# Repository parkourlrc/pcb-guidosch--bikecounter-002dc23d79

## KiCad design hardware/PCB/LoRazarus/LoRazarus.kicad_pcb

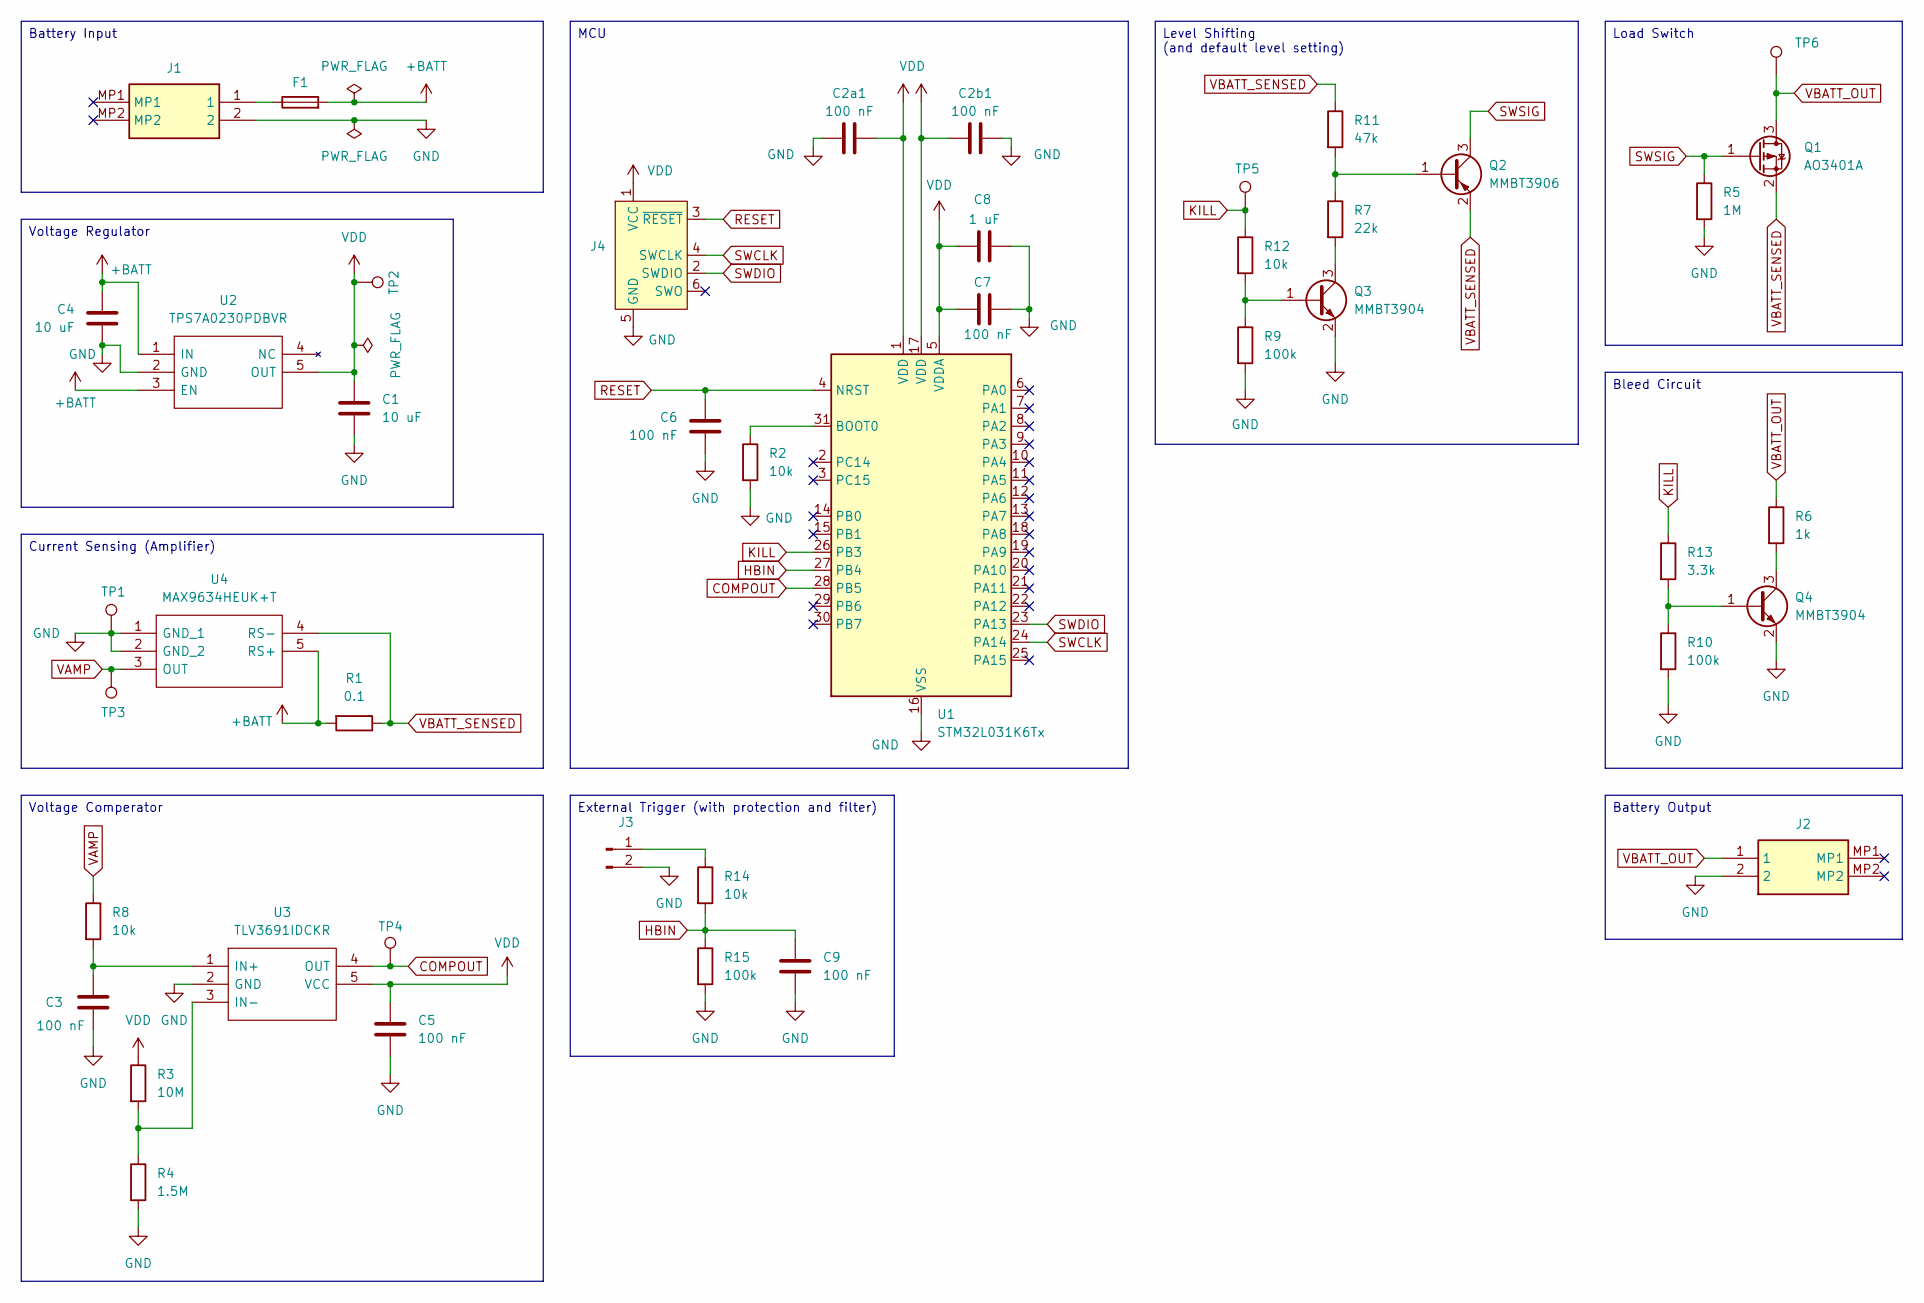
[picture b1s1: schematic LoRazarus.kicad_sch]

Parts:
C1, C4: 10 uF; C_0805_2012Metric
C2a1, C2b1, C3, C5, C6, C7, C9: 100 nF; C_0603_1608Metric
C8: 1 uF; C_0603_1608Metric
F1: Fuse; Fuse_1206_3216Metric
J1, J2: S2B-PH-SM4-TB_LF__SN_; S2BPHSM4TBLFSN; Mouser Part Number N/A
J3: Conn_01x02_Pin; PinHeader_1x02_P2.54mm_Vertical
J4: Conn_ARM_SWD_TagConnect_TC2030-NL; Tag-Connect_TC2030-IDC-NL_2x03_P1.27mm_Vertical
Q1: AO3401A; SOT-23
Q2: MMBT3906; SOT-23
Q3, Q4: MMBT3904; SOT-23
R1: 0.1; R_1206_3216Metric
R2, R8, R12, R14: 10k; R_0603_1608Metric
R3: 10M; R_0603_1608Metric
R4: 1.5M; R_0603_1608Metric
R5: 1M; R_0603_1608Metric
R6: 1k; R_0603_1608Metric
R7: 22k; R_0603_1608Metric
R9, R10, R15: 100k; R_0603_1608Metric
R11: 47k; R_0603_1608Metric
R13: 3.3k; R_0603_1608Metric
TP1, TP2, TP3, TP4, TP5, TP6: TestPoint; TestPoint_Pad_1.0x1.0mm
U1: STM32L031K6Tx; LQFP-32_7x7mm_P0.8mm
U2: TPS7A0230PDBVR; SOT-23-5; Mouser Part Number 595-TPS7A0230PDBVR
U3: TLV3691IDCKR; SOT-353_SC-70-5; Mouser Part Number 595-TLV3691IDCKR
U4: MAX9634HEUK+T; SOT-23-5; Mouser Part Number 700-MAX9634HEUKT

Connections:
+BATT: C4.1, F1.2, R1.2, U2.1 (IN), U2.3 (EN), U4.5 (RS+)
COMPOUT: TP4.1 (1_1), U1.28 (PB5), U3.4 (OUT)
GND: C1.2, C2a1.2, C2b1.2, C3.2, C4.2, C5.2, C6.2, C7.2, C8.2, C9.2, J1.2, J2.2, J3.2, J4.5 (GND), Q3.2 (E), Q4.2 (E), R2.2, R4.2, R5.2, R9.2, R10.2, R15.2, TP1.1 (1_1), U1.16 (VSS), U1.32 (VSS), U2.2 (GND), U3.2 (GND), U4.1 (GND_1), U4.2 (GND_2)
HBIN: C9.1, R14.2, R15.1, U1.27 (PB4)
KILL: R12.1, R13.1, TP5.1 (1_1), U1.26 (PB3)
unnamed: F1.1, J1.1
unnamed: J3.1, R14.1
unnamed: Q2.1 (B), R7.1, R11.2
unnamed: Q3.1 (B), R9.1, R12.2
unnamed: Q3.3 (C), R7.2
unnamed: Q4.1 (B), R10.1, R13.2
unnamed: Q4.3 (C), R6.2
unnamed: R2.1, U1.31 (BOOT0)
unnamed: C3.1, R8.2, U3.1 (IN+)
unnamed: R3.2, R4.1, U3.3 (IN-)
RESET: C6.1, J4.3 (~RESET), U1.4 (NRST)
SWCLK: J4.4 (SWCLK), U1.24 (PA14)
SWDIO: J4.2 (SWDIO), U1.23 (PA13)
SWSIG: Q1.1 (G), Q2.3 (C), R5.1
VAMP: R8.1, TP3.1 (1_1), U4.3 (OUT)
VBATT_OUT: J2.1, Q1.3 (D), R6.1, TP6.1 (1_1)
VBATT_SENSED: Q1.2 (S), Q2.2 (E), R1.1, R11.1, U4.4 (RS-)
VDD: C1.1, C2a1.1, C2b1.1, C5.1, C7.1, C8.1, J4.1 (VCC), R3.1, TP2.1 (1_1), U1.1 (VDD), U1.5 (VDDA), U1.17 (VDD), U2.5 (OUT), U3.5 (VCC)

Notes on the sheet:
Battery Input
External Trigger (with protection and filter)
Battery Output
Load Switch
Voltage Regulator
Level Shifting (and default level setting)
Current Sensing (Amplifier)
MCU
Bleed Circuit
Voltage Comperator

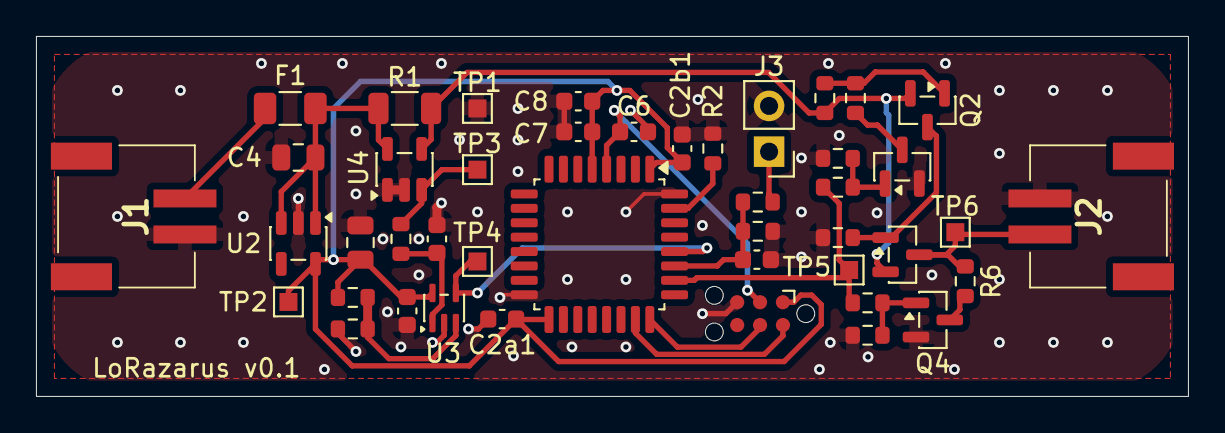
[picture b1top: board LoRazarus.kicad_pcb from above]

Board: 2 copper layers, 64.0 x 20.0 mm, 44 parts (0 on the bottom side), 23 nets.
